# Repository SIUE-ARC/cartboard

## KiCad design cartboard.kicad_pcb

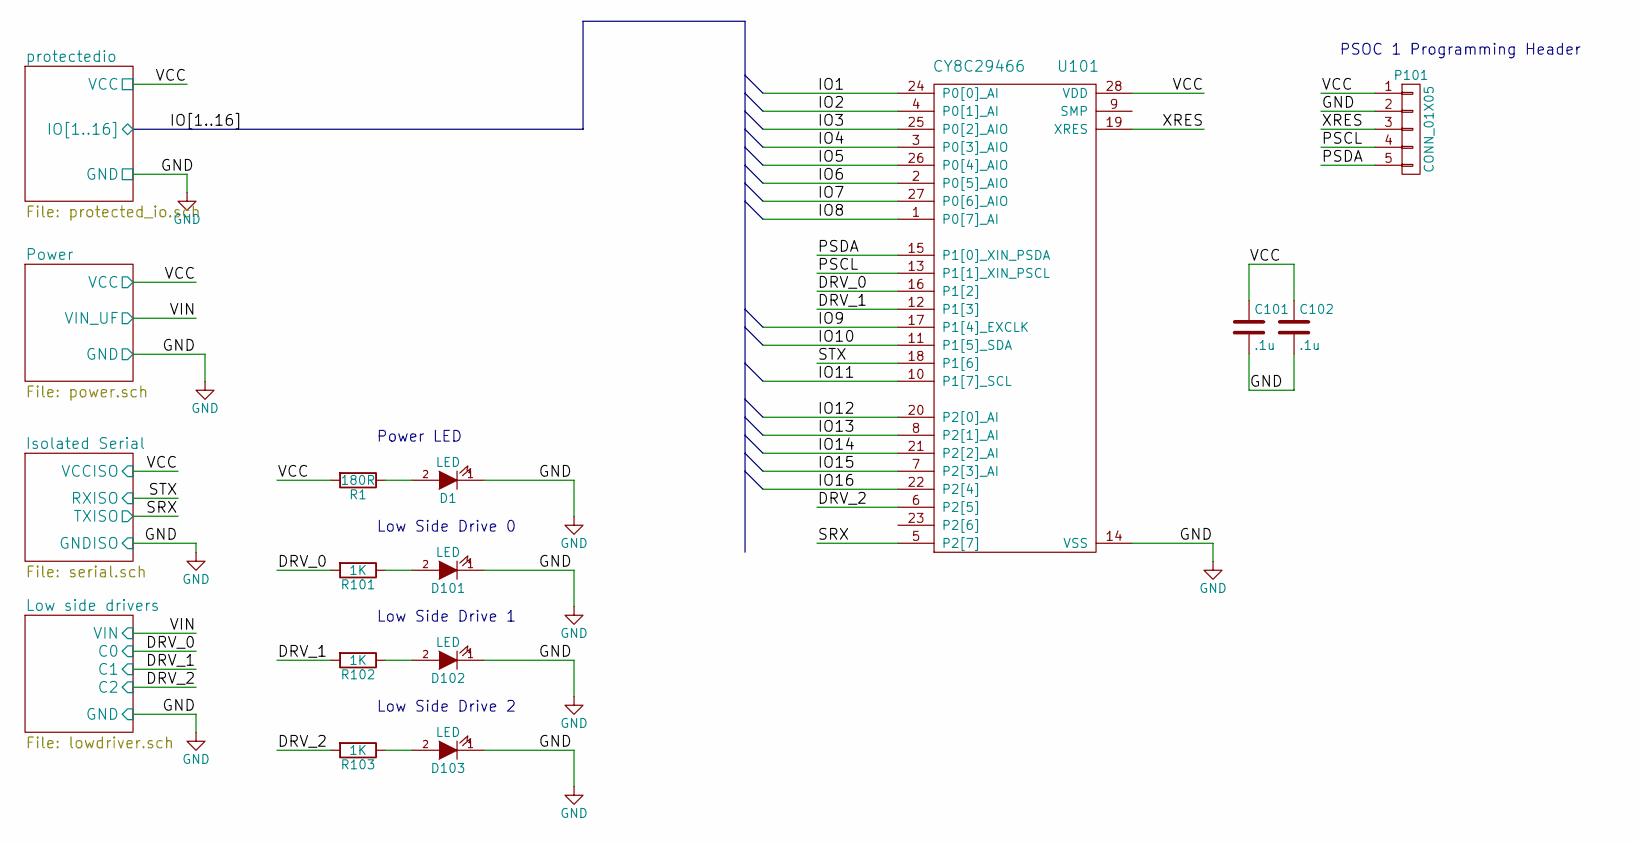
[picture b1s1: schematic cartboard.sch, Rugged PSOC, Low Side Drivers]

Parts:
C101, C102: .1u; C_0603_HandSoldering
D1, D101, D102, D103: LED; LED_0805; Part APT2012SGC
P101: CONN_01X05; Pin_Header_Angled_1x05; Part WM4203-ND
R1: 180R; R_0603_HandSoldering
R101, R102, R103: 1K; R_0603_HandSoldering
U101: CY8C29466; SSOP-28_5.3x10.2mm_Pitch0.65mm

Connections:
/IO1: U101.24 (P0[0]_AI); also elsewhere on the board
/IO2: U101.4 (P0[1]_AI); also elsewhere on the board
/IO3: U101.25 (P0[2]_AIO); also elsewhere on the board
/IO4: U101.3 (P0[3]_AIO); also elsewhere on the board
/IO5: U101.26 (P0[4]_AIO); also elsewhere on the board
/IO6: U101.2 (P0[5]_AIO); also elsewhere on the board
/IO7: U101.27 (P0[6]_AIO); also elsewhere on the board
/IO8: U101.1 (P0[7]_AI); also elsewhere on the board
/IO9: U101.17 (P1[4]_EXCLK); also elsewhere on the board
/IO10: U101.11 (P1[5]_SDA); also elsewhere on the board
/IO11: U101.10 (P1[7]_SCL); also elsewhere on the board
/IO12: U101.20 (P2[0]_AI); also elsewhere on the board
/IO13: U101.8 (P2[1]_AI); also elsewhere on the board
/IO14: U101.21 (P2[2]_AI); also elsewhere on the board
/IO15: U101.7 (P2[3]_AI); also elsewhere on the board
/IO16: U101.22 (P2[4]); also elsewhere on the board
/Isolated Serial/RXISO: U101.18 (P1[6]); also elsewhere on the board
/Isolated Serial/TXISO: U101.5 (P2[7]); also elsewhere on the board
/Low side drivers/C0: R101.2, U101.16 (P1[2]); also elsewhere on the board
/Low side drivers/C1: R102.2, U101.12 (P1[3]); also elsewhere on the board
/Low side drivers/C2: R103.2, U101.6 (P2[5]); also elsewhere on the board
/PSCL: P101.4, U101.13 (P1[1]_XIN_PSCL)
/PSDA: P101.5, U101.15 (P1[0]_XIN_PSDA)
/Power/VCC: C101.1, C102.1, P101.1, R1.2, U101.28 (VDD); also elsewhere on the board
/XRES: P101.3, U101.19 (XRES)
GND: C101.2, C102.2, D1.1 (K), D101.1 (K), D102.1 (K), D103.1 (K), P101.2, U101.14 (VSS); also elsewhere on the board
unnamed: D1.2 (A), R1.1
unnamed: D101.2 (A), R101.1
unnamed: D102.2 (A), R102.1
unnamed: D103.2 (A), R103.1

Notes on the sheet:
PSOC 1 Programming Header
Power LED
Low Side Drive 0
Low Side Drive 1
Low Side Drive 2

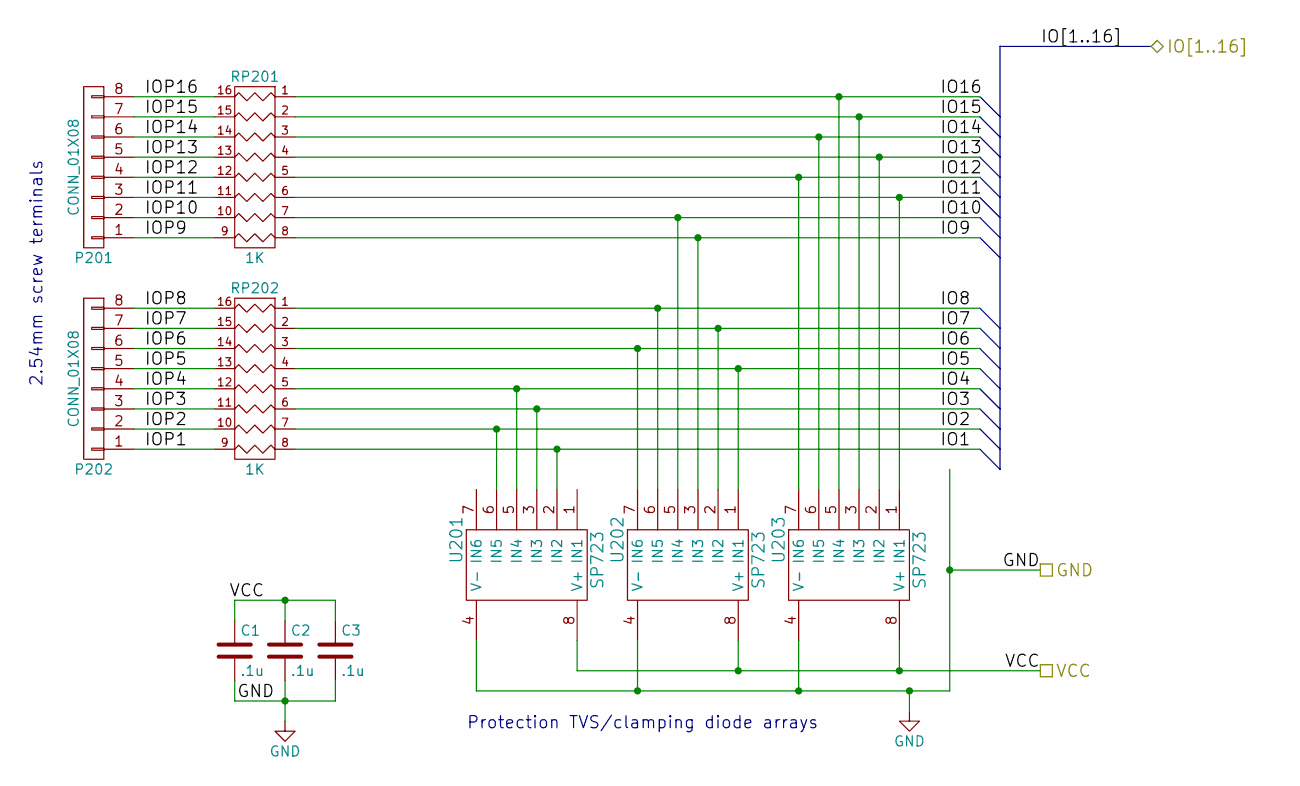
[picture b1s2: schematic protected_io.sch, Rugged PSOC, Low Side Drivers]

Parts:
C1, C2, C3: .1u; C_0603_HandSoldering
P201, P202: CONN_01X08; TE_TERMBLOCK_5mmx8_282836-8; Part 282836-8
RP201, RP202: 1K; SOIC-16_7.5x10.3mm_Pitch1.27mm; Part 628A102
U201, U202, U203: SP723; SOIC-8_3.9x4.9mm_Pitch1.27mm

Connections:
/IO1: RP202.8, U201.2 (IN2); also elsewhere on the board
/IO2: RP202.7, U201.6 (IN5); also elsewhere on the board
/IO3: RP202.6, U201.3 (IN3); also elsewhere on the board
/IO4: RP202.5, U201.5 (IN4); also elsewhere on the board
/IO5: RP202.4, U202.1 (IN1); also elsewhere on the board
/IO6: RP202.3, U202.7 (IN6); also elsewhere on the board
/IO7: RP202.2, U202.2 (IN2); also elsewhere on the board
/IO8: RP202.1, U202.6 (IN5); also elsewhere on the board
/IO9: RP201.8, U202.3 (IN3); also elsewhere on the board
/IO10: RP201.7, U202.5 (IN4); also elsewhere on the board
/IO11: RP201.6, U203.1 (IN1); also elsewhere on the board
/IO12: RP201.5, U203.7 (IN6); also elsewhere on the board
/IO13: RP201.4, U203.2 (IN2); also elsewhere on the board
/IO14: RP201.3, U203.6 (IN5); also elsewhere on the board
/IO15: RP201.2, U203.3 (IN3); also elsewhere on the board
/IO16: RP201.1, U203.5 (IN4); also elsewhere on the board
/Power/VCC: C1.1, C2.1, C3.1, U201.8 (V+), U202.8 (V+), U203.8 (V+); also elsewhere on the board
/protectedio/IOP1: P202.1, RP202.9 (R8)
/protectedio/IOP2: P202.2, RP202.10 (R7)
/protectedio/IOP3: P202.3, RP202.11 (R6)
/protectedio/IOP4: P202.4, RP202.12 (R5)
/protectedio/IOP5: P202.5, RP202.13 (R4)
/protectedio/IOP6: P202.6, RP202.14 (R3)
/protectedio/IOP7: P202.7, RP202.15 (R2)
/protectedio/IOP8: P202.8, RP202.16 (R1)
/protectedio/IOP9: P201.1, RP201.9 (R8)
/protectedio/IOP10: P201.2, RP201.10 (R7)
/protectedio/IOP11: P201.3, RP201.11 (R6)
/protectedio/IOP12: P201.4, RP201.12 (R5)
/protectedio/IOP13: P201.5, RP201.13 (R4)
/protectedio/IOP14: P201.6, RP201.14 (R3)
/protectedio/IOP15: P201.7, RP201.15 (R2)
/protectedio/IOP16: P201.8, RP201.16 (R1)
GND: C1.2, C2.2, C3.2, U201.4 (V-), U202.4 (V-), U203.4 (V-); also elsewhere on the board

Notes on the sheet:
Protection TVS/clamping diode arrays
2.54mm screw terminals

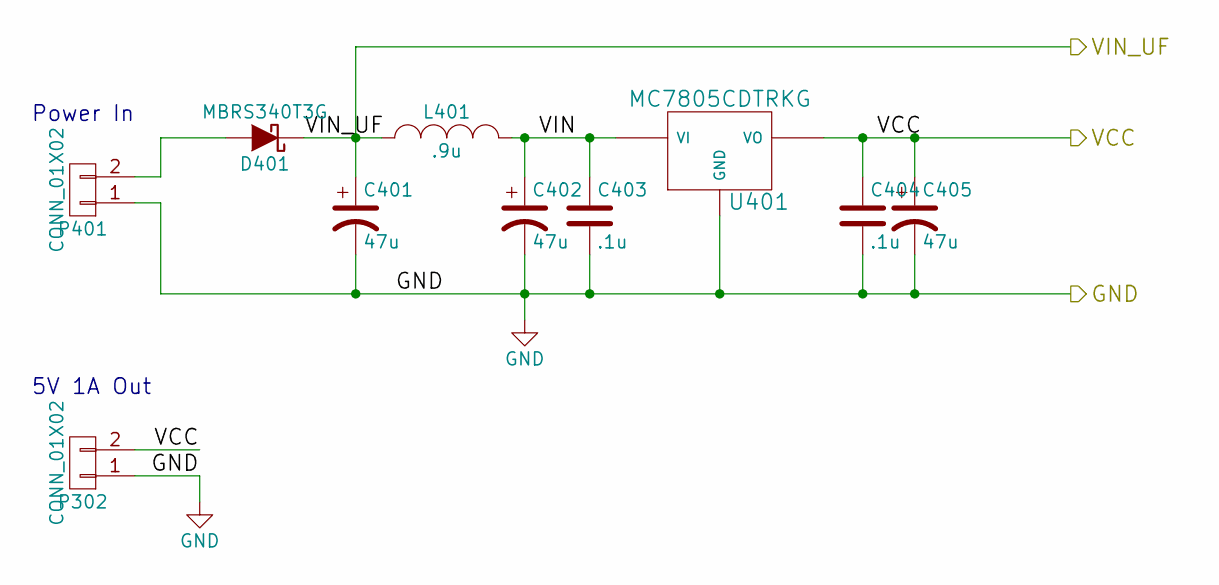
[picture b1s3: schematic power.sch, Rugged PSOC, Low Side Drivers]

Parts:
C401, C402, C405: 47u; CAP_UCD1H470MCL6GS; part UCD1H470MCL6GS
C403, C404: .1u; C_0603_HandSoldering
D401: MBRS340T3G; SMC_Standard; Part MBRS340T3G
L401: .9u; L_NRS; Part NRS6028T0R9NMGJV
P302, P401: CONN_01X02; TE_TERMBLOCK_5mmx2_282836-2; Part ED2609-ND
U401: MC7805CDTRKG; D-PAK3

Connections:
/Low side drivers/VIN: C401.1, D401.1 (K), L401.1; also elsewhere on the board
/Power/VCC: C404.1, C405.1, P302.2, U401.3 (VO); also elsewhere on the board
/Power/VIN: C402.1, C403.1, L401.2, U401.1 (VI)
GND: C401.2, C402.2, C403.2, C404.2, C405.2, P302.1, P401.1, U401.4 (GND); also elsewhere on the board
unnamed: D401.2 (A), P401.2

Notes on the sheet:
Power In
5V 1A Out

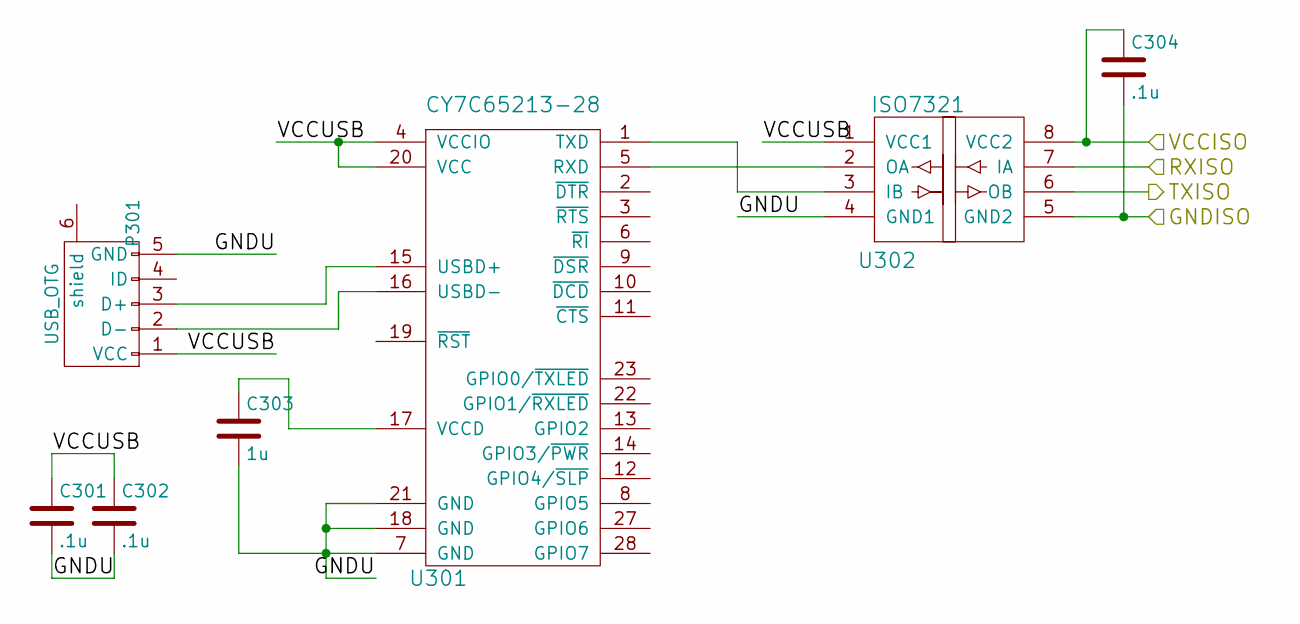
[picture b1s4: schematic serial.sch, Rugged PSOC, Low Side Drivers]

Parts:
C301, C302, C304: .1u; C_0603_HandSoldering
C303: 1u; C_0603_HandSoldering
P301: USB_OTG; USB_Mini-B; Part 65100516121
U301: CY7C65213-28; SSOP-28_5.3x10.2mm_Pitch0.65mm; Part CY7C65213-28PVXI
U302: ISO7321; SOIJ-8_5.3x5.3mm_Pitch1.27mm

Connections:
/Isolated Serial/GNDU: C301.2, C302.2, C303.2, P301.5 (GND), U301.7 (GND), U301.18 (GND), U301.21 (GND), U302.4 (GND1)
/Isolated Serial/RXISO: U302.7 (IA); also elsewhere on the board
/Isolated Serial/TXISO: U302.6 (OB); also elsewhere on the board
/Isolated Serial/VCCUSB: C301.1, C302.1, P301.1 (VCC), U301.4 (VCCIO), U301.20 (VCC), U302.1 (VCC1)
/Power/VCC: C304.1, U302.8 (VCC2); also elsewhere on the board
GND: C304.2, U302.5 (GND2); also elsewhere on the board
unnamed: C303.1, U301.17 (VCCD)
unnamed: P301.2 (D-), U301.16 (USBD-)
unnamed: P301.3 (D+), U301.15 (USBD+)
unnamed: U301.1 (TXD), U302.3 (IB)
unnamed: U301.5 (RXD), U302.2 (OA)

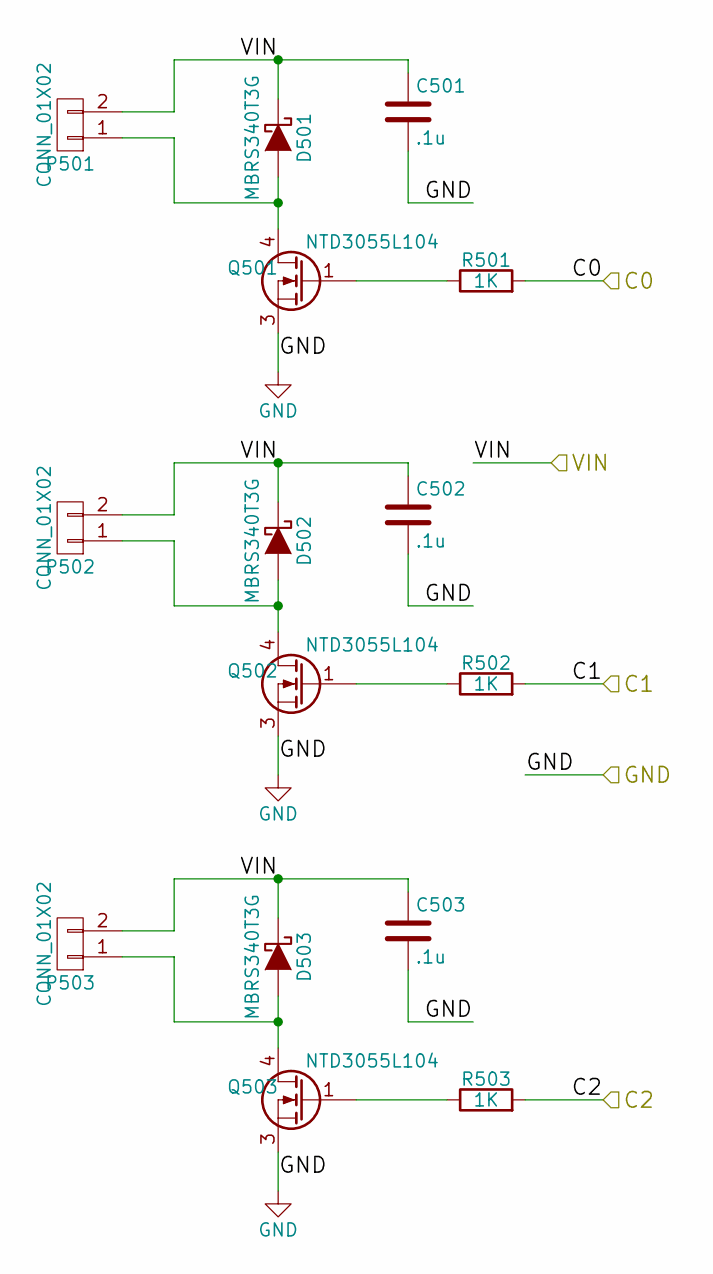
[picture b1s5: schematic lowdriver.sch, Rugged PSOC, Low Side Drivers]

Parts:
C501, C502, C503: .1u; C_0603_HandSoldering
D501, D502, D503: MBRS340T3G; SMC_Standard
P501, P502, P503: CONN_01X02; TE_TERMBLOCK_5mmx2_282836-2
Q501, Q502, Q503: NTD3055L104; D-PAK3
R501, R502, R503: 1K; R_0603_HandSoldering

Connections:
/Low side drivers/C0: R501.2; also elsewhere on the board
/Low side drivers/C1: R502.2; also elsewhere on the board
/Low side drivers/C2: R503.2; also elsewhere on the board
/Low side drivers/VIN: C501.1, C502.1, C503.1, D501.1 (K), D502.1 (K), D503.1 (K), P501.2, P502.2, P503.2; also elsewhere on the board
GND: C501.2, C502.2, C503.2, Q501.3 (S), Q502.3 (S), Q503.3 (S); also elsewhere on the board
unnamed: D501.2 (A), P501.1, Q501.4 (D)
unnamed: D502.2 (A), P502.1, Q502.4 (D)
unnamed: D503.2 (A), P503.1, Q503.4 (D)
unnamed: Q501.1 (G), R501.1
unnamed: Q502.1 (G), R502.1
unnamed: Q503.1 (G), R503.1

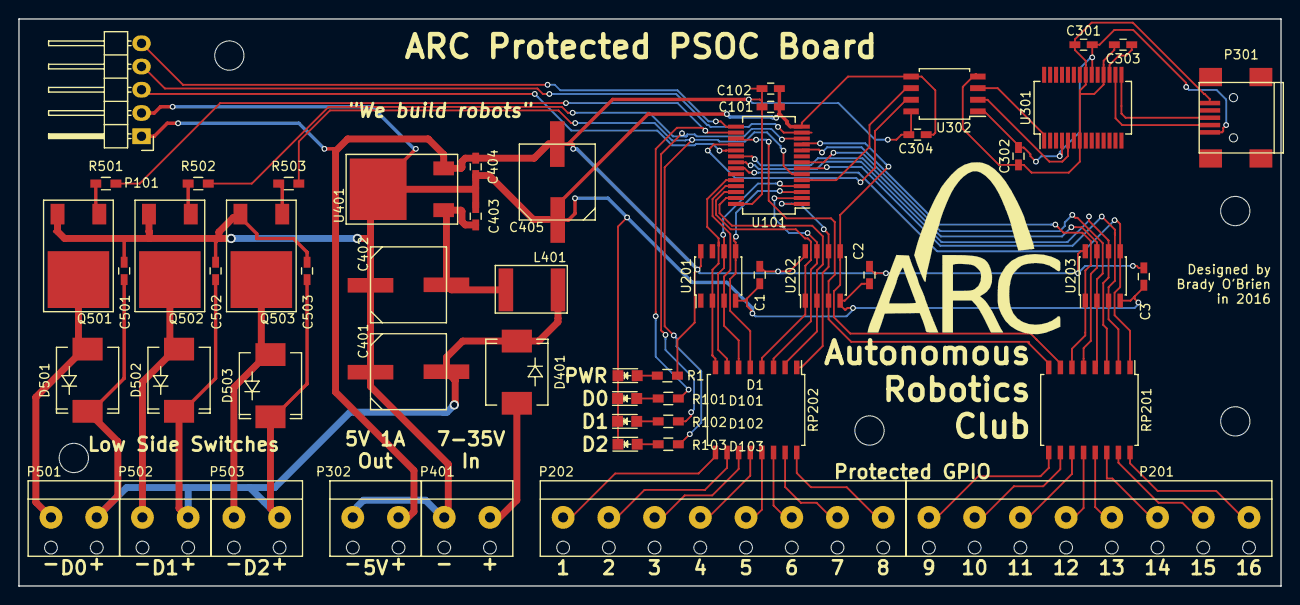
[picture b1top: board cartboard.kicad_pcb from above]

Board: 2 copper layers, 138.0 x 62.0 mm, 59 parts (0 on the bottom side), 62 nets.

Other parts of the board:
MH1, MH1#2, MH1#3, MH1#4, MH1#5: MountingHole_3.2mm_M3

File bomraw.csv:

Reference, Value, Footprint, Part,Digikey Part Number,Count
C1 C2 C3 C101 C102 C403 C404 C301 C302 C303 C304 C501 C502 C503,.1u,Capacitors_SMD:C_0603_HandSoldering,CC0603ZRY5V9BB104,311-1343-1-ND,13
L401,.9u,cartboard:L_NRS,NRS6028T0R9NMGJV,587-3633-1-ND,1
RP201 RP202,1K,Resistors_SMD:R_Array_Convex_8x0602,EXB-2HV102JV,Y1102CT-ND,2
R501 R502 R503,1K,Resistors_SMD:R_0603_HandSoldering,RC0603FR-071KL,311-1.00KHRCT-ND,3
C401 C402 C405,47u,cartboard:CAP_UCD1H470MCL6GS,UCD1H470MCL6GS,493-6184-1-ND,3
P302 P401 P501 P502 P503,CONN_01X02,cartboard:SCREW_1x2_5.08mm,OSTTC022162,ED2609-ND,5
P101,CONN_01X05,,22232051,WM4203-ND,1
P201 P202,CONN_01X08,cartboard:TERM_BLOCK_1x8_2.54,OSTVN08A150,ED10566-ND,2
U301,CY7C65213-28,Housings_SSOP:SSOP-28_5.3x10.2mm_Pitch0.65mm,CY7C65213-28PVXI,CY7C65213-28PVXI-ND,1
U101,CY8C29466,Housings_SSOP:SSOP-28_5.3x10.2mm_Pitch0.65mm,CY8C29466-24PVXI,428-1587-ND,1
U302,ISO7321,Housings_SOIC:SOIJ-8_5.3x5.3mm_Pitch1.27mm,ISO7321CDR,296-42102-1-ND,1
D401 D501 D502 D503,MBRS340T3G,Diodes_SMD:SMC_Standard,MBRS340T3G,MBRS340T3GOSCT-ND,4
U401,MC7805CDTRKG,cartboard:D-PAK3,MC7805CDTRKG,MC7805CDTRKGOSCT-ND,1
Q501 Q502 Q503,NTD3055L104,cartboard:D-PAK3,NTD3055L104T4G,NTD3055L104T4GOSCT-ND,3
U201 U202 U203,SP723,Housings_SOIC:SOIC-8_3.9x4.9mm_Pitch1.27mm,SP723ABG,F2721-ND,3
P301,USB_OTG,Connect:USB_Mini-B,690-005-299-043,151-1206-1-ND,1

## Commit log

2016-09-12 First 'release'
2016-09-12 moved BOM into release directory
2016-09-12 cleanup
2016-09-12 Fixed BOM
2016-09-12 Fixed BOM and made pretty PDF BOM
2016-09-12 Changed the silkscreen layers and set a new release
2016-09-12 silkscreen change
2016-09-12 Added TAPR OHL as license
2016-09-22 copied license

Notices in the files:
cartboard.kicad_pcb:
Copyright 2016, Brady O'Brien
Licensed under the TAPR Open Hardware License (www.tapr.org/OHL)
